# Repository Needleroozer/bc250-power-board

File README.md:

# bc250-power-board
Power Distribution PCBs for the BC-250 cards

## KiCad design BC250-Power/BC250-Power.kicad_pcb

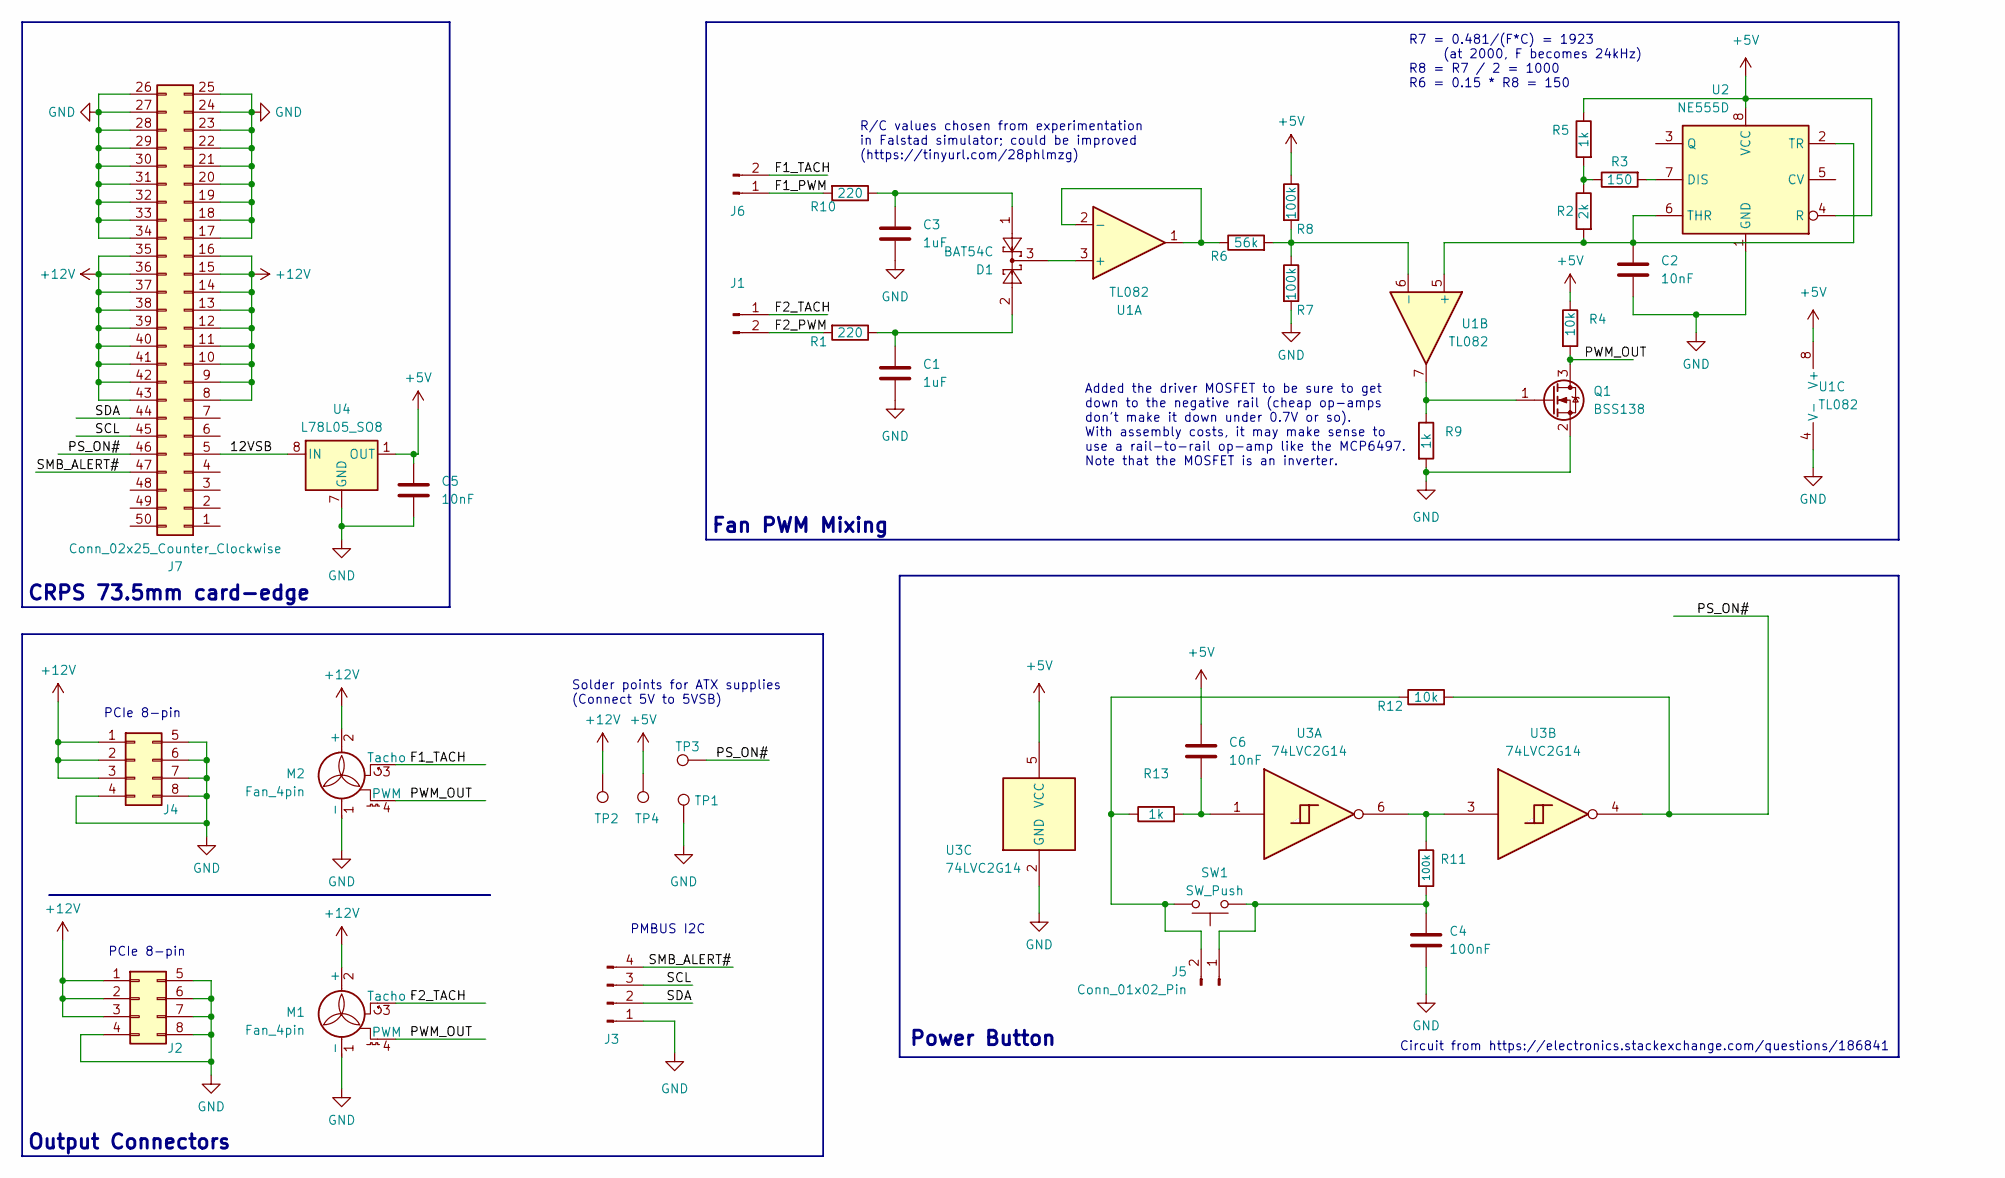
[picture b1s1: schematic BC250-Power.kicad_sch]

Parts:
C1, C3: 1uF; C_0603_1608Metric
C2, C5, C6: 10nF; C_0603_1608Metric
C4: 100nF; C_0603_1608Metric
D1: BAT54C; SOT-23
J1, J5, J6: Conn_01x02_Pin; PinHeader_1x02_P2.54mm_Horizontal
J2, J4: Conn_02x04_Odd_Even; GPU-8P-PCB
J3: Conn_01x04_Pin; PinHeader_1x04_P2.54mm_Horizontal
J7: Conn_02x25_Counter_Clockwise; S-50L-2.54-5
M1, M2: Fan_4pin; FanPinHeader_1x04_P2.54mm_Vertical
Q1: BSS138; SOT-23
R1, R10: 220; R_0603_1608Metric
R2: 2k; R_0603_1608Metric
R3: 150; R_0603_1608Metric
R4, R12: 10k; R_0603_1608Metric
R5, R9, R13: 1k; R_0603_1608Metric
R6: 56k; R_0603_1608Metric
R7, R8, R11: 100k; R_0603_1608Metric
SW1: SW_Push; SW_SPST_TL3305A
TP1, TP2, TP3, TP4: TestPoint; TestPoint_Loop_D2.60mm_Drill1.6mm_Beaded
U1: TL082; SOIC-8_3.9x4.9mm_P1.27mm
U2: NE555D; SOIC-8_3.9x4.9mm_P1.27mm
U3: 74LVC2G14; SOT-23-6
U4: L78L05_SO8; SOIC-8_3.9x4.9mm_P1.27mm

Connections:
+5V: C5.1, C6.1, R4.1, R5.1, R8.1, TP4.1, U1.8 (V+), U2.4 (R), U2.8 (VCC), U3.5 (VCC), U4.1 (OUT)
+12V: J2.1, J2.2, J2.3, J4.1, J4.2, J4.3, J7.8, J7.9, J7.10, J7.11, J7.12, J7.13, J7.14, J7.15, J7.16, J7.35, J7.36, J7.37, J7.38, J7.39, J7.40, J7.41, J7.42, J7.43, M1.2 (+), M2.2 (+), TP2.1
/12VSB: J7.5, U4.8 (IN)
/F1_PWM: J6.1, R10.2
/F1_TACH: J6.2, M2.3 (Tacho)
/F2_PWM: J1.2, R1.2
/F2_TACH: J1.1, M1.3 (Tacho)
/PS_ON#: J7.46, R12.2, TP3.1, U3.4
/PWM_OUT: M1.4 (PWM), M2.4 (PWM), Q1.3 (D), R4.2
/SCL: J3.3, J7.45
/SDA: J3.2, J7.44
/SMB_ALERT#: J3.4, J7.47
GND: C1.2, C2.2, C3.2, C4.2, C5.2, J2.4, J2.5, J2.6, J2.7, J2.8, J3.1, J4.4, J4.5, J4.6, J4.7, J4.8, J7.17, J7.18, J7.19, J7.20, J7.21, J7.22, J7.23, J7.24, J7.25, J7.26, J7.27, J7.28, J7.29, J7.30, J7.31, J7.32, J7.33, J7.34, M1.1 (-), M2.1 (-), Q1.2 (S), R7.2, R9.2, TP1.1, U1.4 (V-), U2.1 (GND), U3.2 (GND), U4.2 (GND), U4.3 (GND), U4.6 (GND), U4.7 (GND)
unnamed: C1.1, D1.2, R1.1
unnamed: C3.1, D1.1, R10.1
unnamed: C6.2, R13.2, U3.1
unnamed: C4.1, J5.1, R11.2, SW1.2
unnamed: J5.2, R12.1, R13.1, SW1.1
unnamed: Q1.1 (G), R9.1, U1.7
unnamed: R2.1, R3.1, R5.2
unnamed: R11.1, U3.3, U3.6
unnamed: D1.3, U1.3 (+)
unnamed: R6.1, U1.1, U1.2 (-)
unnamed: C2.1, R2.2, U1.5 (+), U2.2 (TR), U2.6 (THR)
unnamed: R6.2, R7.1, R8.2, U1.6 (-)
unnamed: R3.2, U2.7 (DIS)

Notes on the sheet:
Output Connectors
R7 = 0.481/(F*C) = 1923 (at 2000, F becomes 24kHz) R8 = R7 / 2 = 1000 R6 = 0.15 * R8 = 150
PCIe 8-pin
Fan PWM Mixing
CRPS 73.5mm card-edge
Power Button
Solder points for ATX supplies (Connect 5V to 5VSB)
Circuit from https://electronics.stackexchange.com/questions/186841
PMBUS I2C
R/C values chosen from experimentation in Falstad simulator; could be improved (https://tinyurl.com/28phlmzg)
Added the driver MOSFET to be sure to get down to the negative rail (cheap op-amps don't make it down under 0.7V or so). With assembly costs, it may make sense to use a rail-to-rail op-amp like the MCP6497. Note that the MOSFET is an inverter.

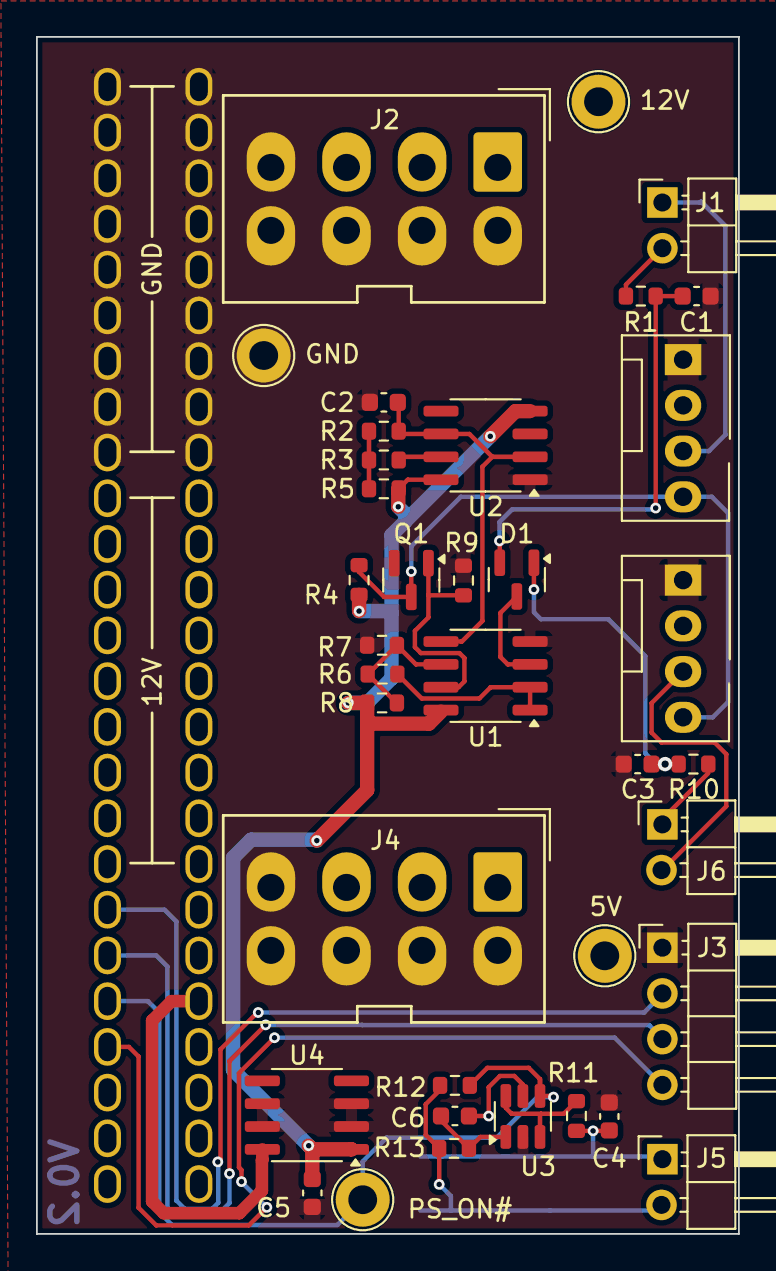
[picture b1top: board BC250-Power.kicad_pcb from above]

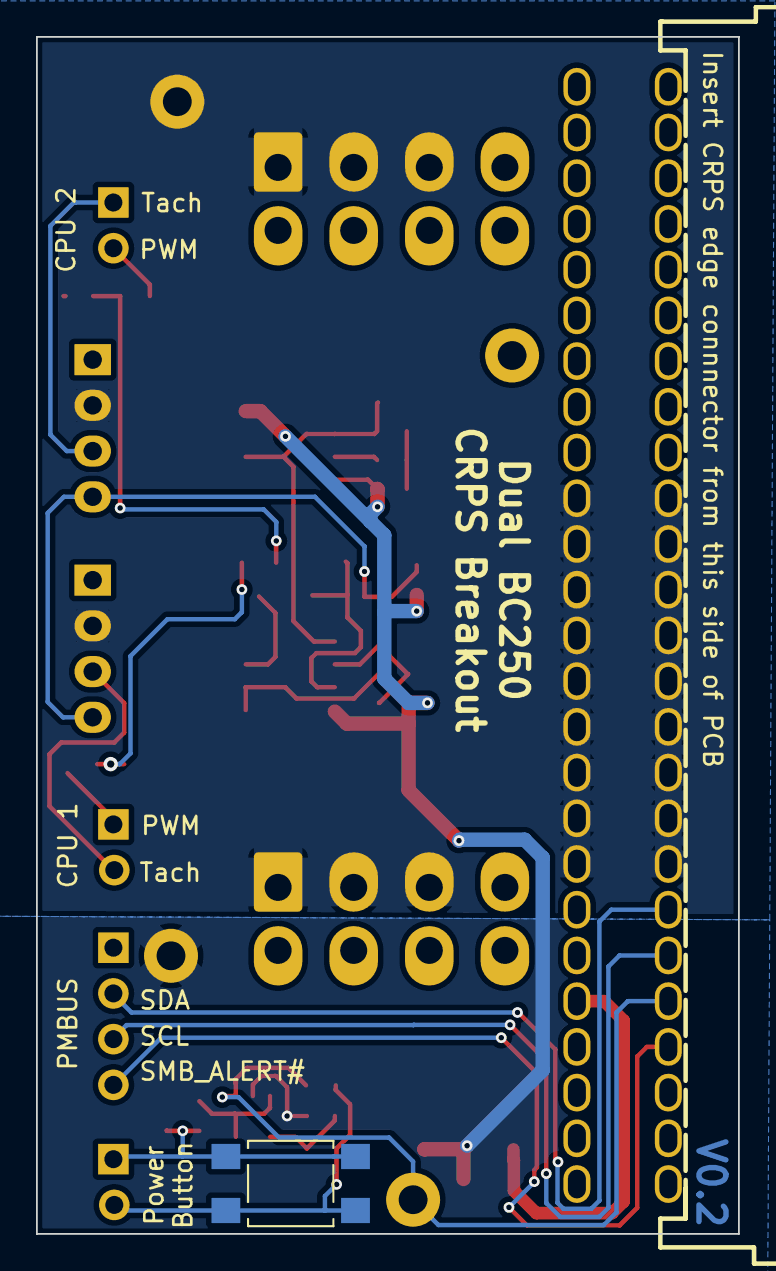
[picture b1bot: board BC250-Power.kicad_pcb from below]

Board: 2 copper layers, 39.0 x 66.5 mm, 39 parts (2 on the bottom side), 26 nets.

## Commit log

2025-03-23 Add CRPS schematic
2025-03-23 Add values for fan circuit passives
2025-03-24 Add card-edge connector design files
2025-03-26 Add and associate S-50L-2.54-5 model
2025-03-26 Update to KiCad 9 and redo holes in card-edge footprint
    Kicad 7 doesn't render shells in STEPs correctly
2025-04-06 Add footprint for zeyeco 8P GPU power receptacle
2025-04-06 Start layout and fix pinning
2025-04-06 First pass at routing
2025-04-18 Add V0.2 of dual BC-250 CRPS breakout
    - Organize fab layer
    - Un-mirror edge connector (was reversing 12VSB and PS_ON# - oops)
